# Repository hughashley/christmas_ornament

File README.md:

# christmas_ornament
repo for schematics and code for 2022 xmas ornament project

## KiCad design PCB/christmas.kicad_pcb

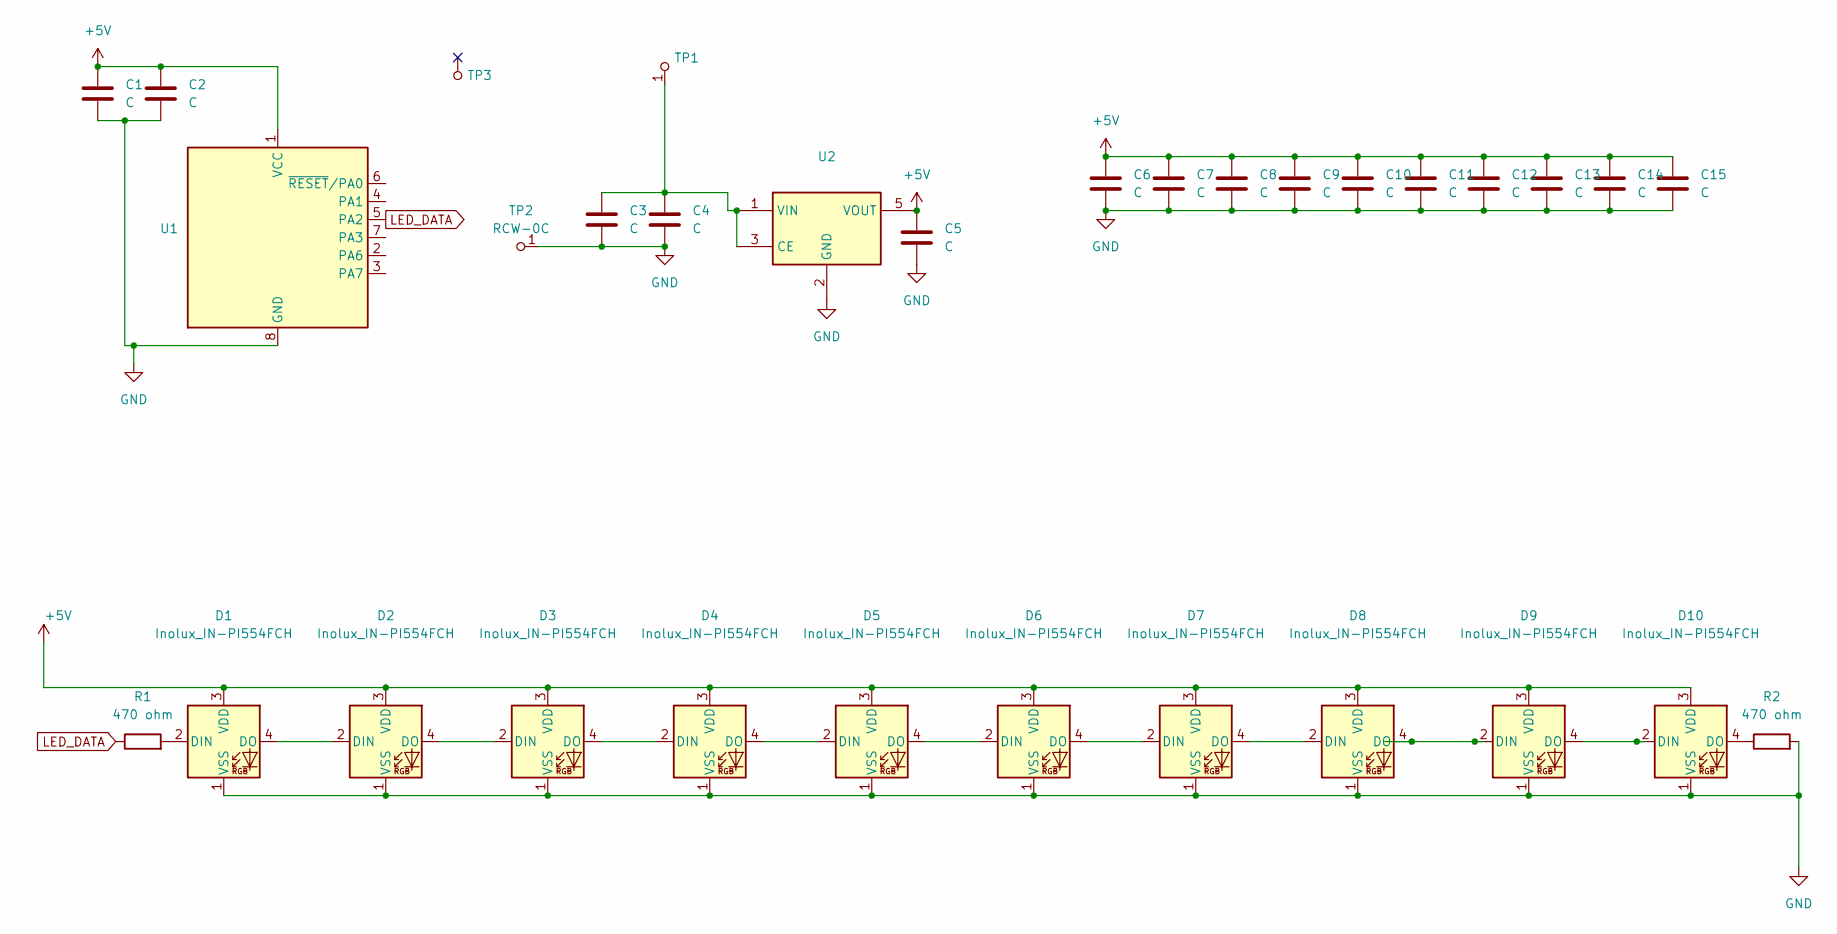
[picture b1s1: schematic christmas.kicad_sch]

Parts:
C1, C2, C3, C4, C5, C6, C7, C8, C9, C10, C11, C12, C13, C14, C15: C
D1, D2, D3, D4, D5, D6, D7, D8, D9, D10: Inolux_IN-PI554FCH; LED_Inolux_IN-PI554FCH_PLCC4_5.0x5.0mm_P3.2mm
R1, R2: 470 ohm
TP1: MPN RCW-0C; Digi-Key_PN A106146CT-ND
TP2: RCW-0C; PROBE_PAD_1206; MPN RCW-0C; Digi-Key_PN A106146CT-ND
TP3: MPN 5001; Digi-Key_PN 36-5001-ND
U1, U2: (no value)

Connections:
+5V: C1.1, C2.1, C5.1, C6.1, C7.1, C8.1, C9.1, C10.1, C11.1, C12.1, C13.1, C14.1, C15.1, D1.3 (VDD), D2.3 (VDD), D3.3 (VDD), D4.3 (VDD), D5.3 (VDD), D6.3 (VDD), D7.3 (VDD), D8.3 (VDD), D9.3 (VDD), D10.3 (VDD), U1.1 (VCC), U2.5 (VOUT)
GND: C1.2, C2.2, C3.1, C4.1, C5.2, C6.2, C7.2, C8.2, C9.2, C10.2, C11.2, C12.2, C13.2, C14.2, C15.2, D1.1 (VSS), D2.1 (VSS), D3.1 (VSS), D4.1 (VSS), D5.1 (VSS), D6.1 (VSS), D7.1 (VSS), D8.1 (VSS), D9.1 (VSS), D10.1 (VSS), R2.2, TP2.1, U1.8 (GND), U2.2 (GND), U2.4 (NC)
LED_DATA: R1.1, U1.5 (PA2)
unnamed: C3.2, C4.2, TP1.1, U2.1 (VIN), U2.3 (CE)
unnamed: D1.2 (DIN), R1.2
unnamed: D1.4 (DO), D2.2 (DIN)
unnamed: D2.4 (DO), D3.2 (DIN)
unnamed: D3.4 (DO), D4.2 (DIN)
unnamed: D4.4 (DO), D5.2 (DIN)
unnamed: D5.4 (DO), D6.2 (DIN)
unnamed: D6.4 (DO), D7.2 (DIN)
unnamed: D7.4 (DO), D8.2 (DIN)
unnamed: D8.4 (DO), D9.2 (DIN)
unnamed: D9.4 (DO), D10.2 (DIN)
unnamed: D10.4 (DO), R2.1

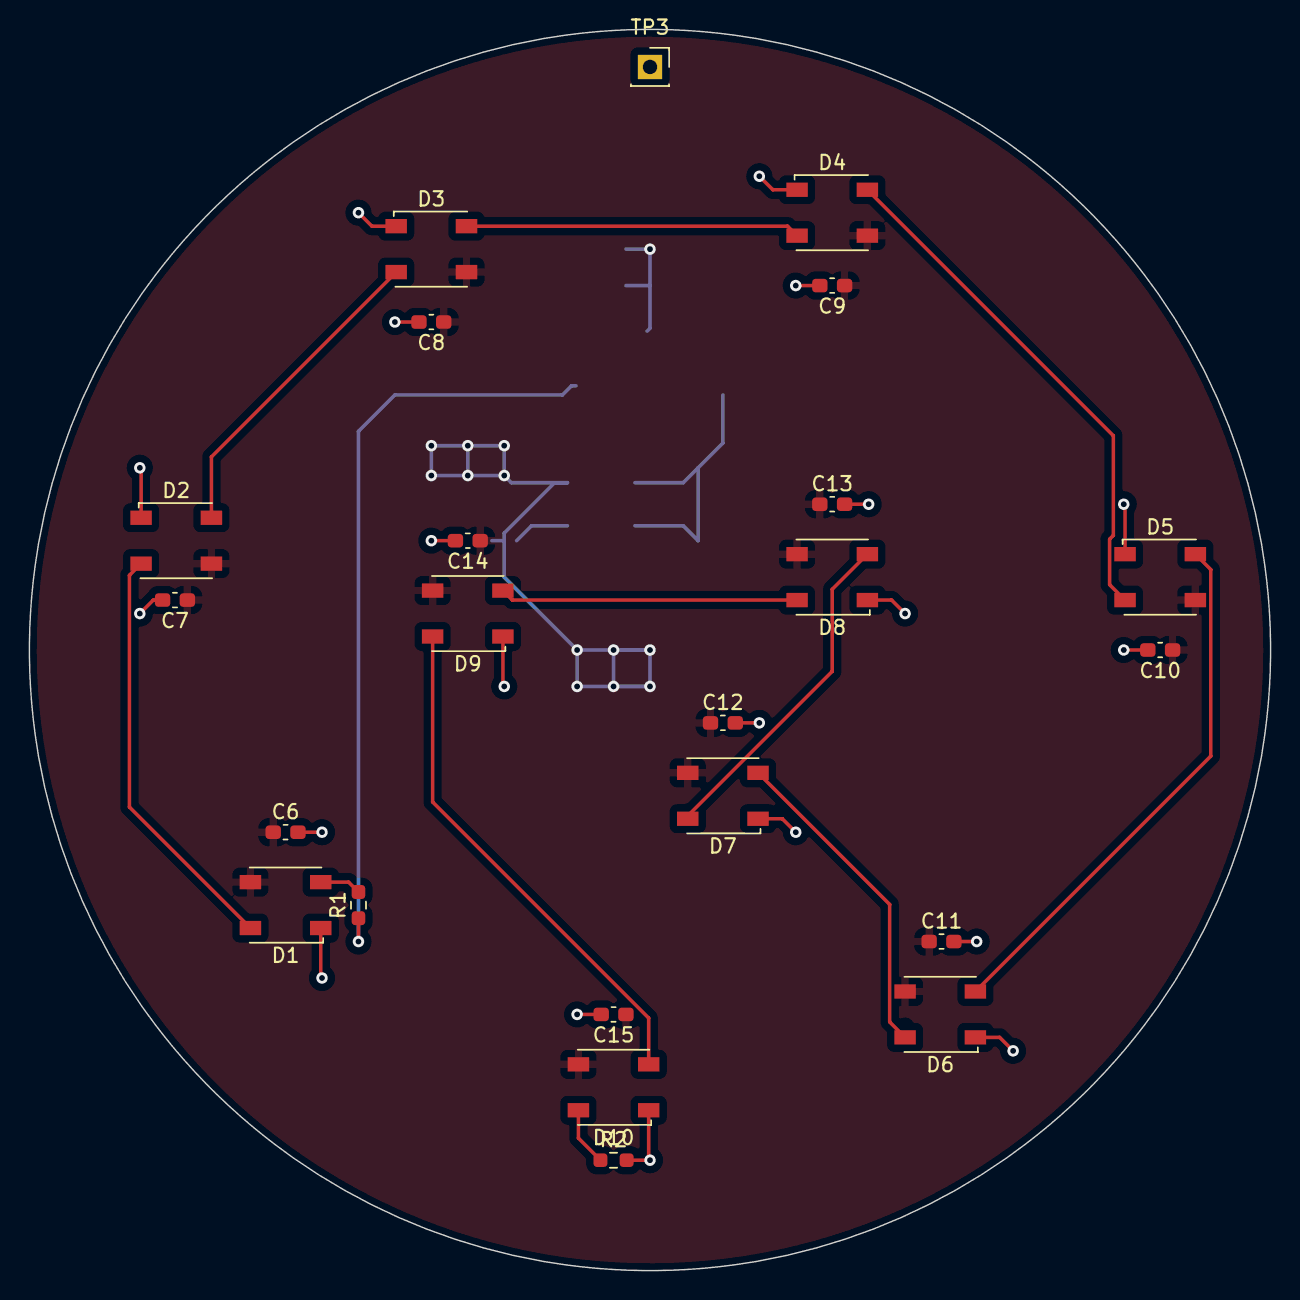
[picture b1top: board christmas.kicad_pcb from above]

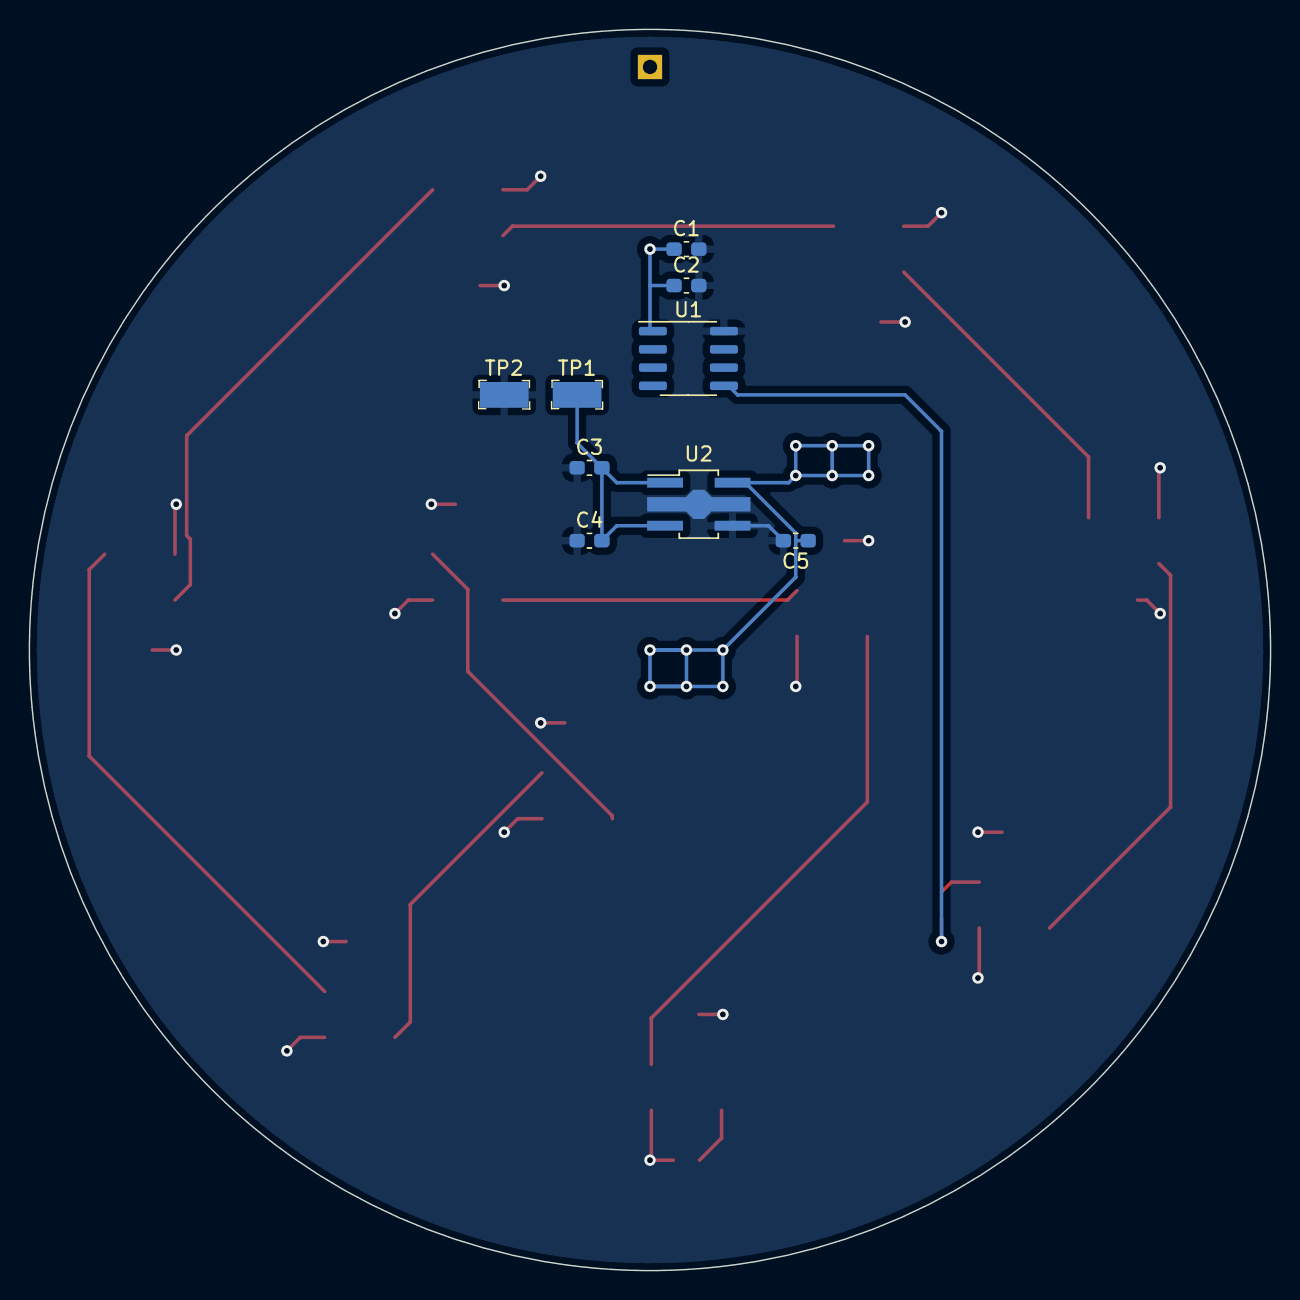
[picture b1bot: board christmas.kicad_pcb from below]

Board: 2 copper layers, 86.5 x 86.5 mm, 32 parts (9 on the bottom side), 15 nets.

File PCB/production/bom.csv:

Designator,Footprint,Quantity,Value,LCSC Part #
"C1, C10, C11, C12, C13, C14, C15, C2, C3, C4, C5, C6, C7, C8, C9",C_0603_1608Metric_Pad1.08x0.95mm_HandSolder,15,C,
"D1, D10, D2, D3, D4, D5, D6, D7, D8, D9",LED_Inolux_IN-PI554FCH_PLCC4_5.0x5.0mm_P3.2mm,10,Inolux_IN-PI554FCH,
"R1, R2",R_0603_1608Metric_Pad0.98x0.95mm_HandSolder,2,470 ohm,
"TP1, TP2",PROBE_PAD_1206,2,RCW-0C,RCW-0C
TP3,PinSocket_1x01_P2.54mm_Vertical,1,5001,5001
U1,SOIC-8_3.9x4.9mm_P1.27mm,1,ATtiny402-SS,
U2,SOT-89-5_Handsoldering,1,XC6210B332MR,
